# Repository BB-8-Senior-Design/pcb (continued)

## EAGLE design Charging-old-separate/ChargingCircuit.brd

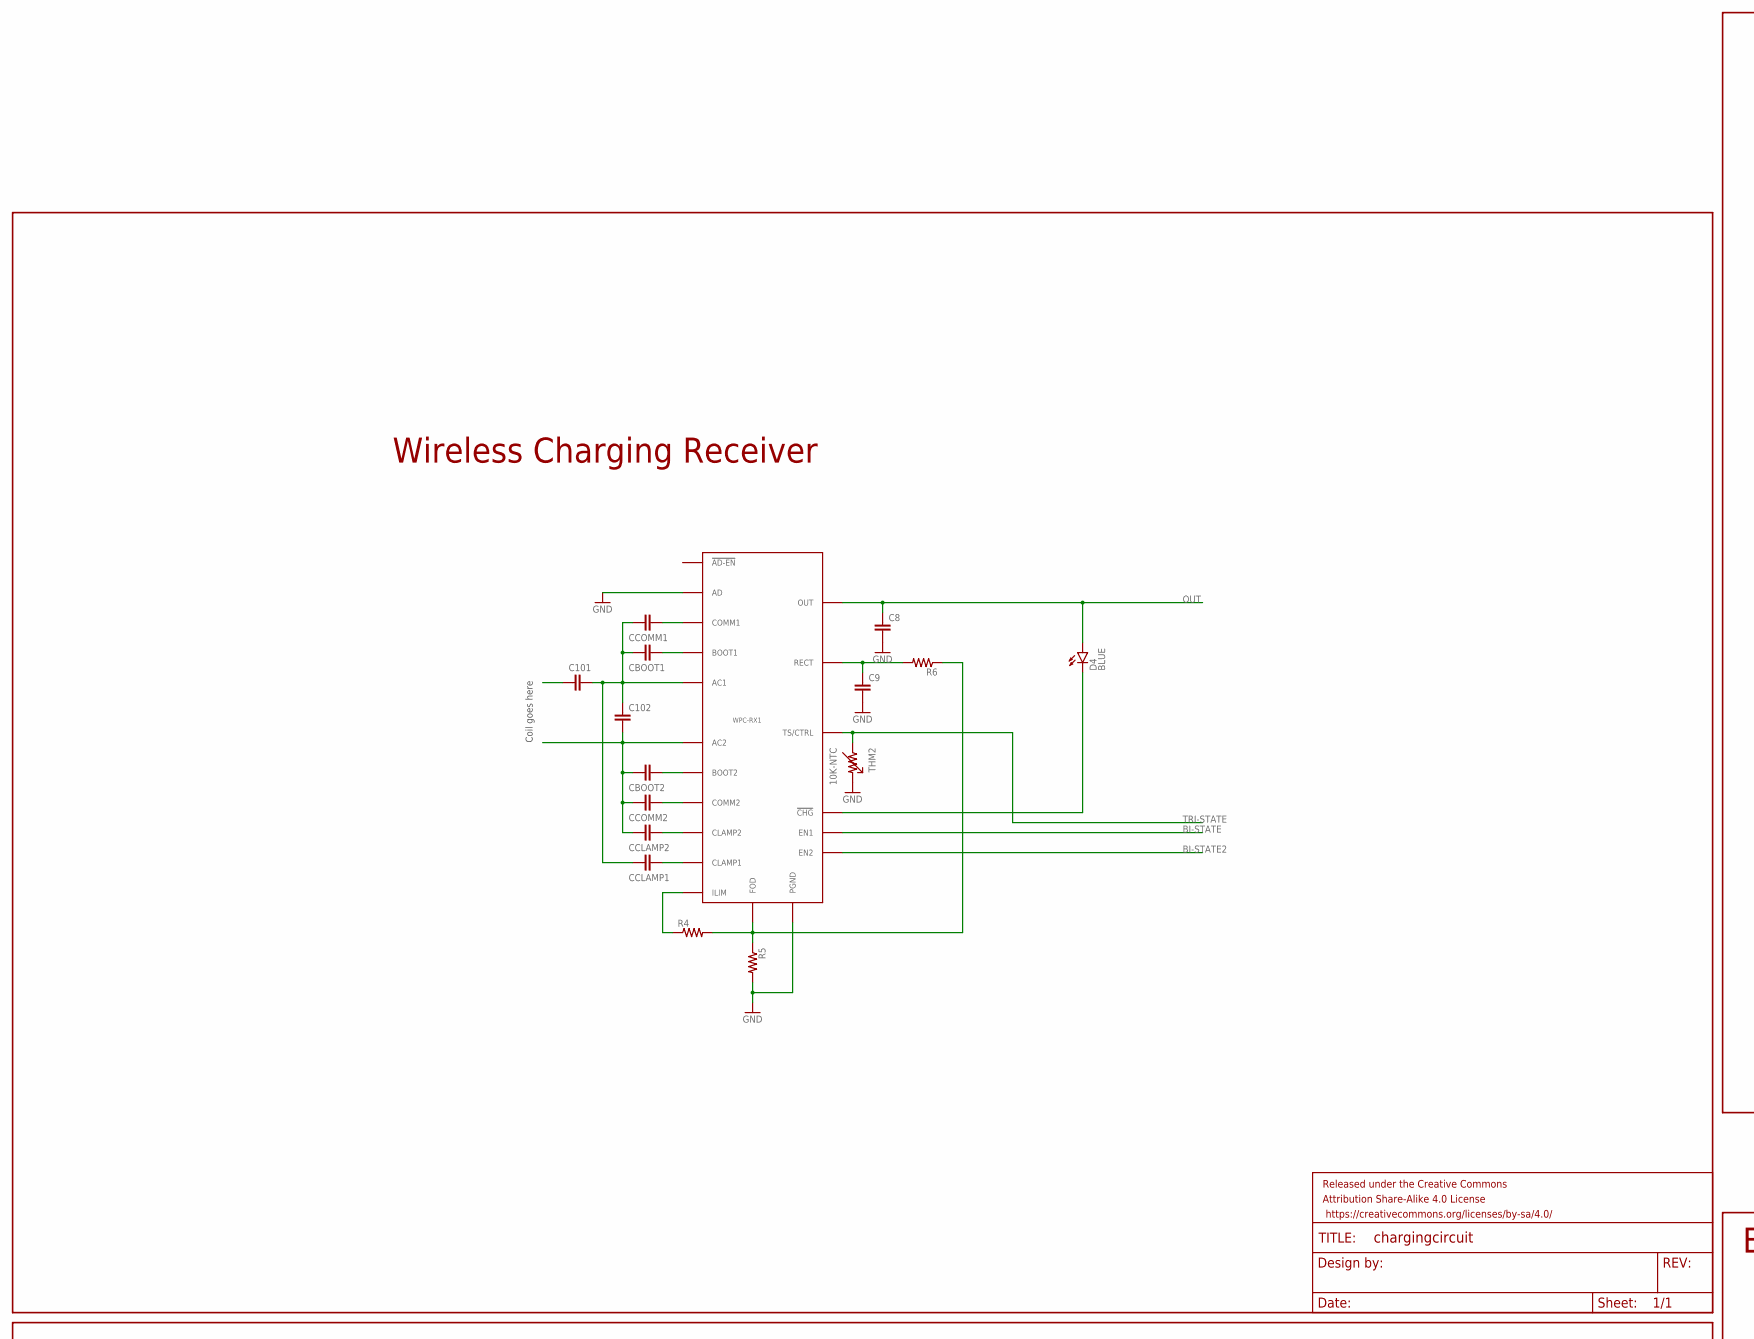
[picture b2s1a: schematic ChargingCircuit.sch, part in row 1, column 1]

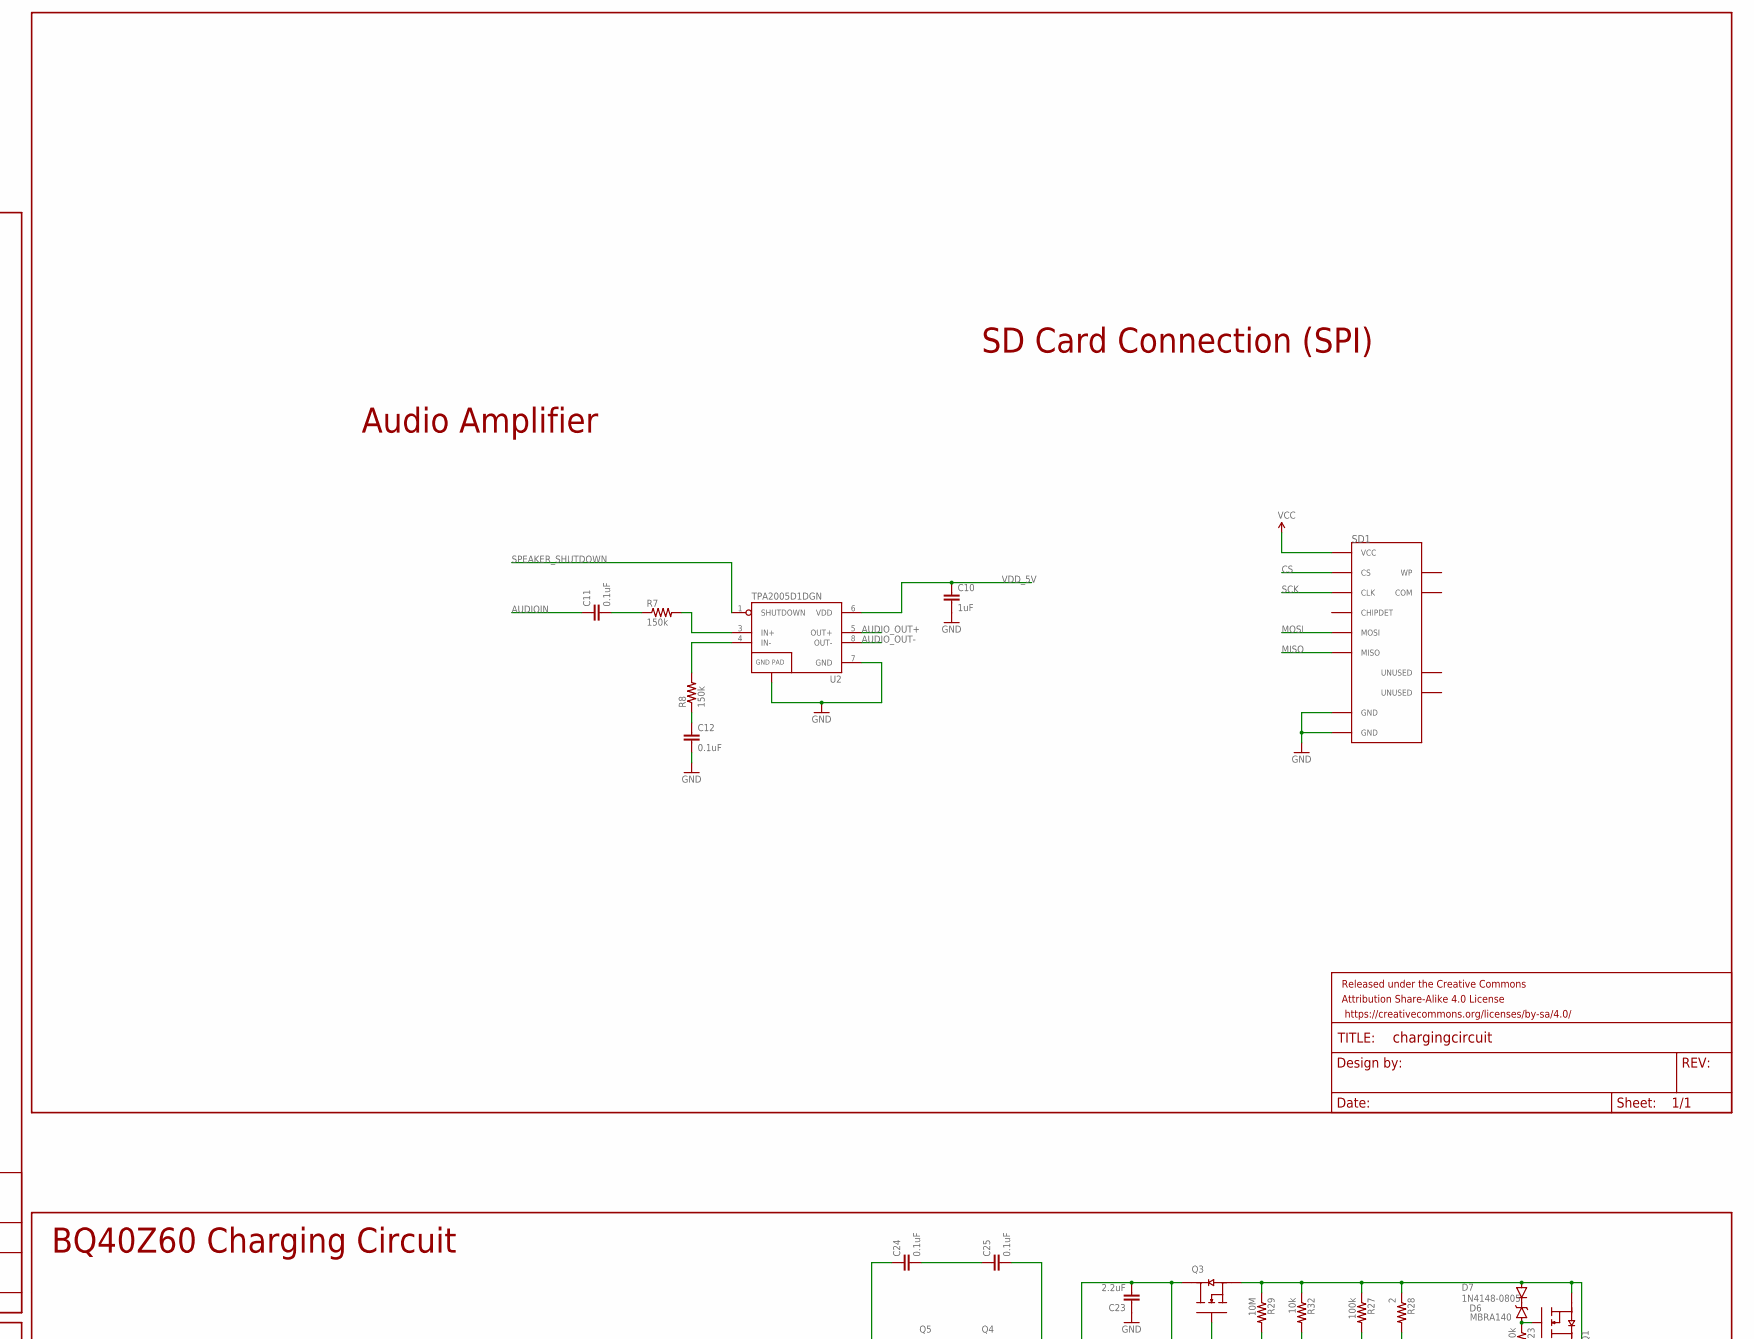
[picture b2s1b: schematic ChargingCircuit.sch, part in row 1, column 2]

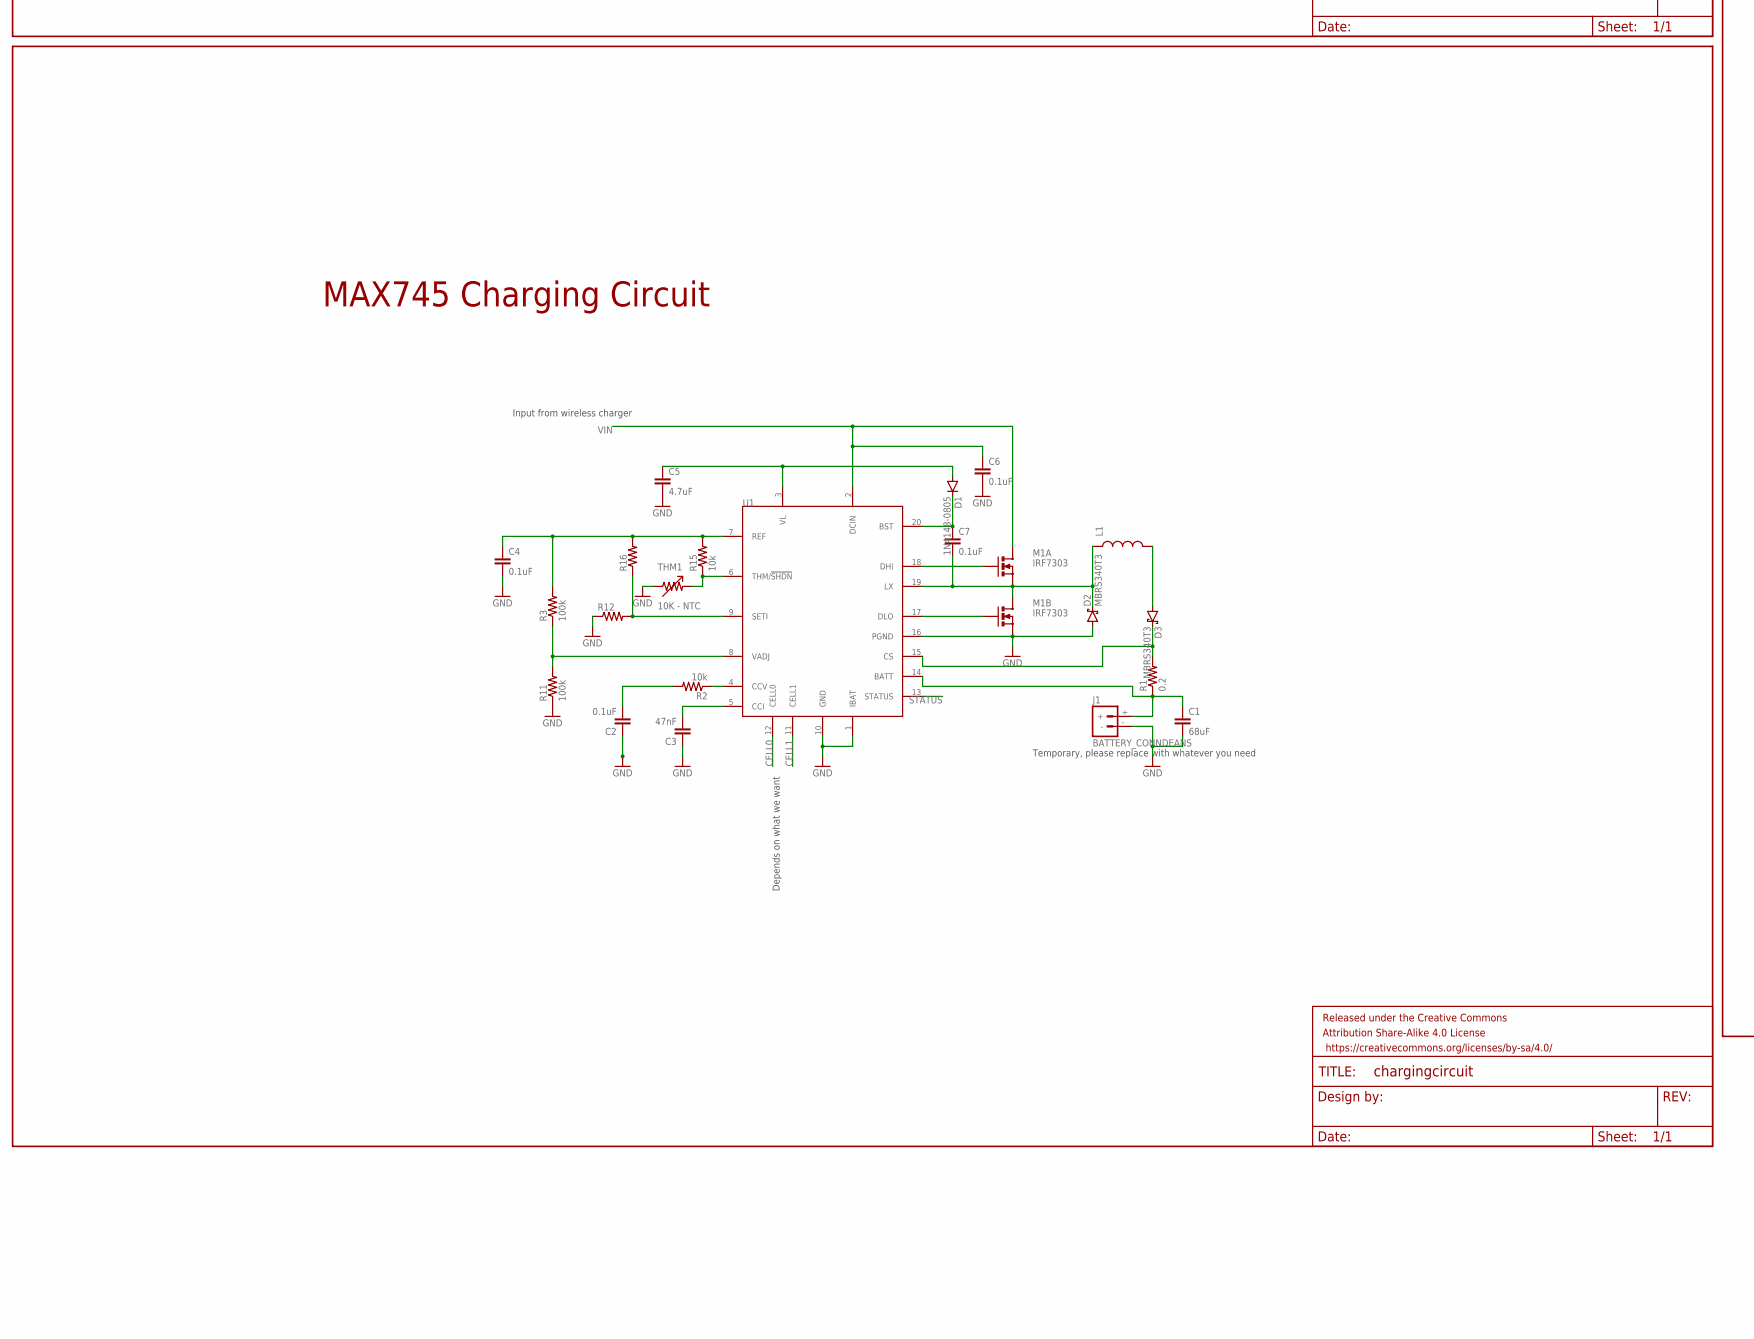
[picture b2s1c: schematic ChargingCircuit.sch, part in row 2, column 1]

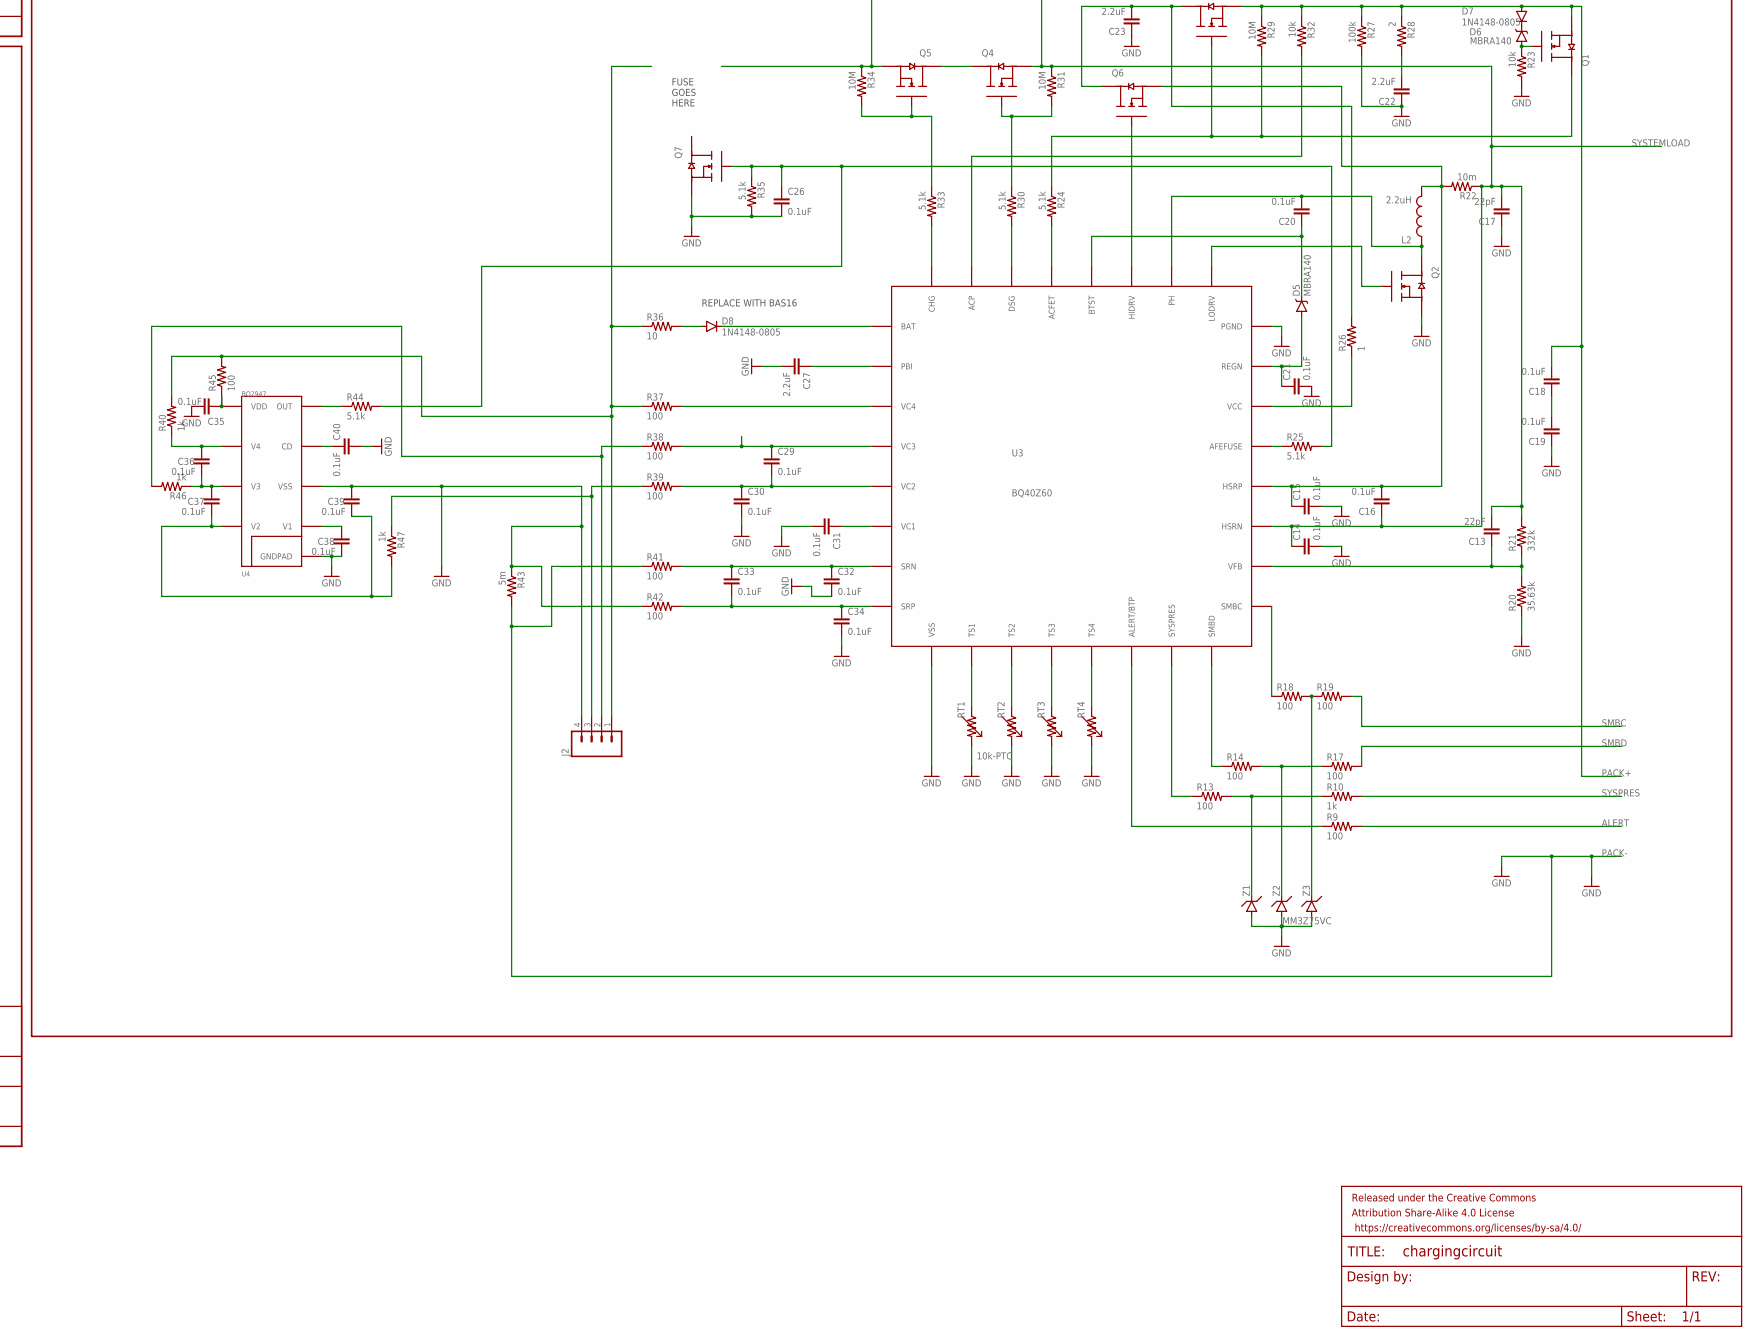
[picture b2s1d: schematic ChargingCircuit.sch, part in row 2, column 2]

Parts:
C1: 68uF; 0805
C2, C4, C6, C7, C11, C12, C14, C15, C16, C18, C19, C20, C21, C24, C25, C26, C29, C30, C31, C32, C33, C34, C35, C36, C37, C38, C39, C40: 0.1uF; 0805
C3: 47nF; 0805
C5: 4.7uF; 0805
C8, C9, C101, C102: CAP0805; 0805
C10: 1uF; 0805
C13, C17: 22pF; 0805
C22, C23, C27: 2.2uF; 0805
CBOOT1, CBOOT2: CAP0805; 0805
CCLAMP1, CCLAMP2: CAP0805; 0805
CCOMM1, CCOMM2: CAP0805; 0805
D1, D7, D8: 1N4148-0805; 0805-DIODE
D2, D3: MBRS340T3; DO-214AB
D4: BLUE; LED-0603
D5, D6: MBRA140; SMA-DIODE
FRAME6, FRAME7, FRAME8, FRAME9: FRAME-LEDGER; CREATIVE_COMMONS
J1: BATTERY_CONNDEANS; DEANS
J2: M04JST; 1X04-1.5MM_JST
L1: INDUCTOR0805; 0805
L2: 2.2uH; 0805
M1: IRF7303; SO08
Q1, Q2, Q3, Q4, Q5, Q6, Q7: CSD17308Q3; SON-8
R1: 0.2; 0805
R2, R15, R23, R32: 10k; 0805
R3, R11, R27: 100k; 0805
R4, R5, R6, R12, R16: RESISTOR0805-RES; 0805
R7, R8: 150k; 0805
R9, R13, R14, R17, R18, R19, R37, R38, R39, R41, R42, R45: 100; 0805
R10, R40, R46, R47: 1k; 0805
R20: 35.63k; 0805
R21: 332k; 0805
R22: 10m; 0805
R24, R25, R30, R33, R35, R44: 5.1k; 0805
R26: 1; 0805
R28: 2; 0805
R29, R31, R34: 10M; 0805
R36: 10; 0805
R43: 5m; 0805
RT1: 10k-PTC; 0805
RT2, RT3, RT4: THM; 0805
SD1: 5738-SDCARD; SD-5738
THM1: 10K - NTC; 0805
THM2: 10K-NTC; 0805
U1: MAX745EACSSOP; SSOP20
U2: TPA2005D1DGN; POWER-SOP8
U3: BQ40Z60; S-PVQFN-N32
U4: BQ2947; WSON-8
WPC-RX1: BQ51013B-20VQFN; 20-VQFN
Z1, Z2, Z3: MM3Z75VC; SOD-323F

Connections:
AC1: C101.2, C102.1, CBOOT1.1, CCLAMP1.1, CCOMM1.1, WPC-RX1.P$2 (AC1)
AC2: C102.2, CBOOT2.1, CCLAMP2.1, CCOMM2.1, WPC-RX1.P$19 (AC2)
ALERT: R9.2
AUDIOIN: C11.1
AUDIO_OUT+: U2.5 (OUT+)
AUDIO_OUT-: U2.8 (OUT-)
BI-STATE: WPC-RX1.P$10 (EN1)
BI-STATE2: WPC-RX1.P$11 (EN2)
BOOT2: CBOOT2.2, WPC-RX1.P$17 (BOOT2)
CELL0: U1.12 (CELL0)
CELL1: U1.11 (CELL1)
CS: SD1.P$1 (CS)
GND: C1.2, C2.1, C3.1, C4.2, C5.2, C6.2, C8.2, C9.2, C10.2, C12.2, C14.2, C15.2, C17.1, C19.1, C21.2, C22.1, C23.1, C26.2, C27.2, C30.2, C31.2, C32.2, C34.2, C35.2, C38.2, C39.1, C40.2, D2.POS (A), J1.-, J2.4, M1.3 (S), Q2.P$1 (S1), Q2.P$2 (S1), Q2.P$3 (S1), Q7.P$1 (S1), Q7.P$2 (S1), Q7.P$3 (S1), R5.2, R11.1, R12.1, R20.1, R23.2, R27.2, R35.2, R42.1, R43.1, RT1.2, RT2.2, RT3.2, RT4.2, SD1.P$3 (GND), SD1.P$6 (GND), THM1.1, THM2.2, U1.1 (IBAT), U1.10 (GND), U1.16 (PGND), U2.7 (GND), U2.9 (GND), U3.P$9 (VSS), U3.P$24 (PGND), U3.P$GND (VSS), U4.P$6 (VSS), U4.P$GND (GNDPAD), WPC-RX1.P$1 (PGND), WPC-RX1.P$9 (AD), WPC-RX1.P$20 (PGND), Z1.1 (A), Z2.1 (A), Z3.1 (A)
MISO: SD1.P$7 (MISO)
MOSI: SD1.P$2 (MOSI)
unnamed: C5.1, D1.1 (A), U1.3 (VL)
unnamed: C7.1, D1.2 (C), U1.20 (BST)
unnamed: M1.2 (G), U1.18 (DHI)
unnamed: M1.4 (G), U1.17 (DLO)
unnamed: D3.NEG (C), R1.2, U1.15 (CS)
unnamed: D3.POS (A), L1.2
unnamed: C1.1, J1.+, R1.1, U1.14 (BATT)
unnamed: C7.2, D2.NEG (C), L1.1, M1.1 (S), M1.5 (D), M1.6 (D), U1.19 (LX)
unnamed: C3.2, U1.5 (CCI)
unnamed: R2.1, U1.4 (CCV)
unnamed: C2.2, R2.2
unnamed: C4.1, R3.2, R15.2, R16.2, U1.7 (REF)
unnamed: R12.2, R16.1, U1.9 (SETI)
unnamed: R15.1, THM1.2, U1.6 (THM/!SHDN)
unnamed: R3.1, R11.2, U1.8 (VADJ)
unnamed: CCOMM2.2, WPC-RX1.P$15 (COMM2)
unnamed: CCLAMP2.2, WPC-RX1.P$16 (CLAMP2)
unnamed: CCLAMP1.2, WPC-RX1.P$5 (CLAMP1)
unnamed: CBOOT1.2, WPC-RX1.P$3 (BOOT1)
unnamed: CCOMM1.2, WPC-RX1.P$6 (COMM1)
unnamed: R4.1, WPC-RX1.P$12 (ILIM)
unnamed: R4.2, R5.1, R6.1, WPC-RX1.P$14 (FOD)
unnamed: D4.C, WPC-RX1.P$7 (!CHG)
unnamed: C9.1, R6.2, WPC-RX1.P$18 (RECT)
unnamed: R7.2, U2.3 (IN+)
unnamed: C11.2, R7.1
unnamed: R10.1, R13.2, Z1.2 (C)
unnamed: R8.2, U2.4 (IN-)
unnamed: RT1.1, U3.P$10 (TS1)
unnamed: C12.1, R8.1
unnamed: RT2.1, U3.P$11 (TS2)
unnamed: RT3.1, U3.P$12 (TS3)
unnamed: RT4.1, U3.P$13 (TS4)
unnamed: R9.1, U3.P$14 (ALERT/BTP)
unnamed: Q1.P$5 (D1), Q1.P$6 (D1), Q1.P$7 (D1), Q1.P$8 (D1), Q3.P$4 (G1), R24.1, R29.2
unnamed: R13.1, U3.P$15 (SYSPRES)
unnamed: R14.1, U3.P$16 (SMBD)
unnamed: R14.2, R17.1, Z2.2 (C)
unnamed: C13.1, R20.2, R21.1, U3.P$18 (VFB)
unnamed: R24.2, U3.P$29 (ACFET)
unnamed: C18.1, C19.2
unnamed: R18.1, U3.P$17 (SMBC)
unnamed: R18.2, R19.1, Z3.2 (C)
unnamed: C15.1, C16.2, L2.2, Q6.P$1 (S1), Q6.P$2 (S1), Q6.P$3 (S1), R22.2, U3.P$20 (HSRP)
unnamed: R26.1, U3.P$22 (VCC)
unnamed: D6.A, Q1.P$4 (G1), R23.1
unnamed: C20.2, L2.1, Q2.P$5 (D1), Q2.P$6 (D1), Q2.P$7 (D1), Q2.P$8 (D1), U3.P$26 (PH)
unnamed: C20.1, D5.C, U3.P$28 (BTST)
unnamed: C21.1, D5.A, U3.P$23 (REGN)
unnamed: C23.2, Q3.P$5 (D1), Q3.P$6 (D1), Q3.P$7 (D1), Q3.P$8 (D1), Q6.P$5 (D1), Q6.P$6 (D1), Q6.P$7 (D1), Q6.P$8 (D1), R26.2
unnamed: R25.1, U3.P$21 (AFEFUSE)
unnamed: C26.1, Q7.P$4 (G1), R25.2, R35.1, R44.2
unnamed: Q6.P$4 (G1), U3.P$27 (HIDRV)
unnamed: D6.C, D7.2 (C)
unnamed: C22.2, R28.2
unnamed: Q2.P$4 (G1), U3.P$25 (LODRV)
unnamed: R30.2, U3.P$31 (DSG)
unnamed: Q4.P$4 (G1), R30.1, R31.2
unnamed: R32.2, U3.P$30 (ACP)
unnamed: Q4.P$5 (D1), Q4.P$6 (D1), Q4.P$7 (D1), Q4.P$8 (D1), Q5.P$5 (D1), Q5.P$6 (D1), Q5.P$7 (D1), Q5.P$8 (D1)
unnamed: C24.2, C25.1
unnamed: C24.1, Q5.P$1 (S1), Q5.P$2 (S1), Q5.P$3 (S1), R34.1
unnamed: Q5.P$4 (G1), R33.1, R34.2
unnamed: R33.2, U3.P$32 (CHG)
unnamed: C40.1, U4.P$7 (CD)
unnamed: J2.1, R36.1, R37.1, R40.2, R45.2
unnamed: D8.2 (C), U3.P$1 (BAT)
unnamed: D8.1 (A), R36.2
unnamed: C27.1, U3.P$2 (PBI)
unnamed: R37.2, U3.P$3 (VC4)
unnamed: C29.1, R38.2, U3.P$4 (VC3)
unnamed: C29.2, C30.1, R39.2, U3.P$5 (VC2)
unnamed: C31.1, U3.P$6 (VC1)
unnamed: C32.1, C33.1, R41.2, U3.P$7 (SRN)
unnamed: C33.2, C34.1, R42.2, U3.P$8 (SRP)
unnamed: R44.1, U4.P$8 (OUT)
unnamed: C36.1, R40.1, U4.P$2 (V4)
unnamed: J2.2, R38.1, R46.2
unnamed: J2.3, R39.1, R47.1
unnamed: C35.1, R45.1, U4.P$1 (VDD)
unnamed: C36.2, C37.1, R46.1, U4.P$3 (V3)
unnamed: C37.2, C39.2, R47.2, U4.P$4 (V2)
unnamed: C38.1, U4.P$5 (V1)
OUT: C8.1, D4.A, WPC-RX1.P$4 (OUT)
PACK+: C18.2, D7.1 (A), Q1.P$1 (S1), Q1.P$2 (S1), Q1.P$3 (S1), Q3.P$1 (S1), Q3.P$2 (S1), Q3.P$3 (S1), R27.1, R28.1, R29.1, R32.1
PACK-: R41.1, R43.2
SCK: SD1.P$5 (CLK)
SMBC: R19.2
SMBD: R17.2
SPEAKER_SHUTDOWN: U2.1 (SHUTDOWN)
STATUS: U1.13 (STATUS)
SYSPRES: R10.2
SYSTEMLOAD: C13.2, C14.1, C16.1, C17.2, C25.2, Q4.P$1 (S1), Q4.P$2 (S1), Q4.P$3 (S1), R21.2, R22.1, R31.1, U3.P$19 (HSRN)
TRI-STATE: THM2.1, WPC-RX1.P$13 (TS/CTRL)
VDD_5V: C10.1, U2.6 (VDD)
VIN: C6.1, M1.7 (D), M1.8 (D), U1.2 (DCIN)

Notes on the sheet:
MAX745 Charging Circuit
Wireless Charging Receiver
Audio Amplifier
Temporary, please replace with whatever you need
Coil goes here
Input from wireless charger
Depends on what we want
SD Card Connection (SPI)
BQ40Z60 Charging Circuit
REPLACE WITH BAS16
FUSE GOES HERE

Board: 2 copper layers, 133 parts (0 on the bottom side), 94 nets, no tracks yet.

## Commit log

2016-09-17 Initial board
2016-09-18 stuff
2016-09-18 Added more parts
2016-09-18 Added MAX745 circuit to pcb project
2016-09-18 Updated board
2016-09-18 minor changes to charging board
2016-09-19 Started powering micro
2016-09-19 Labeling MCs
2016-09-19 Added leve; translation for motor stuff
2016-09-21 Added oscilator to schematic
2016-09-21 Added wireless charging board, speaker circuit
2016-09-22 Added most remaining STM requirements
2016-09-22 added more info for boards
2016-09-22 added extra oscillator resistor
2016-09-23 More work on SD card stuff; TODO: finish up calculations for charging circuit values
2016-09-23 updated crystals
2016-09-23 added buck regulator
2016-09-23 added jtag
2016-09-23 started adding motors
2016-09-23 finished adding motors
2016-09-23 Added cap values
2016-09-23 Moved parts onto board
2016-09-23 Added BQ40Z60 Charging Circuit
2016-09-23 added IMU
2016-09-23 Preliminary work on BQ40Z60, need to short VC3 and VC4, fix VC1
2016-09-23 Combined boards -- death
2016-09-23 Fixed BQ40Z60 for 3S configuration
2016-09-23 Updated symbols for some parts to show value too
2016-09-23 Moved old charging circuit to directory
2016-09-28 Fixed Charging board 3S connections, connected EVERYTHING to the micro
2016-09-28 Various updates to the board
2016-09-30 Updated some values
2016-10-01 Addded fuses to charger, need to finish
2016-10-03 Finalized parts
2016-10-03 added heartbeat LED to PC13
2016-10-03 Replaced inductor in buck regulator
2016-10-03 Renumbered ALL elements
2016-10-03 Minor moving around
2016-10-03 Preliminary layout for wireless receiver done
2016-10-03 More board movement, things are now more or less clustered now
2016-10-03 More moving things around
2016-10-05 replaced SPI sd to SDIO
2016-10-05 fixed board size
2016-10-05 added switch
2016-10-05 started traces
2016-10-05 initial layout of charging circuit
2016-10-05 added XT60
2016-10-05 Moved the schematic
2016-10-05 LAYOUT AAAAAAAAAAAAAAAAAAAAAAAAAAAAAAAAAAAAAAAAAAAAAAAAAAAAAAAAAAAAAAAAAAAAAAAAAAAAAAAAAAAAAAAAAAAAAAAAAAAAAAAAAAAAAAAAAAAAAAAAAAAAAAAAAAAAAAAAAAAAAAARRRRRRRRRRRRRRRRRRRRRRRRRRRRRRRRRRRRRRRRRGGGGGGGG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
2016-10-06 MORE LAYOUT OH GOD EVERYTHING IS GOING TO FAIL
2016-10-06 removed CC-by-SA text from board
2016-10-06 Smaller vias make me happy
2016-10-06 Minor routing progress. TODO: layout for micro parts
2016-10-06 I... I think I finished routing the charging circuit...
2016-10-06 Added Advanced Circuits design rules
2016-10-06 Changed some rects to pads
2016-10-11 routed and placed decoupling capacitors for micro
2016-10-12 continued power routing and more
2016-10-12 rearranged some stuff
2016-10-12 so much routing
2016-10-12 routed mostly everything
2016-10-12 stuff\
2016-10-13 Fixed via sizes, made routes slightly better angles (thanks, kyle)
2016-10-13 more routing fixes
2016-10-13 Added design rule checker, moved some stuff for clearance
2016-10-13 More minor fixes for the DRC, rerouting things so it doesn't yell at me (as much)
2016-10-13 Fixed 3 drill sizes
2016-10-13 AdRedid gnd to pgnd for wireless charging circuit
2016-10-14 Changed DRC to be 5mil
2016-10-14 Down to 33 clearance errors
2016-10-14 Removed ALL violations
2016-10-14 Fixed overlap issue caused by resizing
2016-10-14 Modified capacitor sizes
2016-10-15 routed LED, added standoffs, and refined routes
2016-10-15 Updated cap pads to be slightly larager for easy soldering
2016-10-15 Removed LEDs and 3 pin header since it wasn't worth trying to route
2016-10-15 added vias connecting top and bottom planes (also CAM output)
2016-10-15 manually added new keepout layers and tstop (Chris check)
2016-10-16 Added thermal vias and rerouted some stuff
2016-10-16 moved passives on speaker IC closer
2016-10-16 fixed clearance errors due to ground planes
2016-10-16 Removed vias from power mosfet
2016-10-16 Final part and layout updates (hopefully)
2016-10-16 added trestrict
2016-10-17 Fixed clearance issues and uploaded new Gerbers
2016-10-17 added another main fuse
2016-10-17 added 3-pole LPF w/cutoff ~16kHz
2016-10-17 slightly larger cap size
2016-10-17 added soldermask to SD pad
2016-10-17 Fixed hole sizes
2016-10-17 made SMB clock longer
2016-10-18 added current limiting resistor
2016-10-18 added cap between V1 and V2 of charging circuit
2016-10-18 final final actually final iteration pls god
2016-11-06 new branch
2016-11-06 removed lots of components
2016-11-06 Added pullup resistors to SD card holder lol
2016-11-06 Added pullup resistor to audio amp circuit and adjusted capacitor values
2016-11-06 Kyle spelled my name wrong
2016-11-06 Made board straight and minor routing
2016-11-06 Changed some weird routes to ground
2016-11-07 Added test points to speaker system
2016-11-07 Added BB-8, made holes in JST-XH connector larger
2016-11-07 Finished board v2???
2016-11-07 Made board straight because kyle why
2016-11-08 added connections to future battery board
2016-11-08 minor angle fixes
2016-11-08 Finished up text for our names
2016-11-08 update from sd-card holes
2016-11-08 moved some tValues and tPlace things around
2016-11-09 Minor adjustments to spacing
2016-11-10 moved some stuff around, kyle please check the board for any final adjustments
2016-11-10 Made board smaller, finished routing, added new test via, ect.
2016-11-10 made SD card traces closer in length
2016-11-10 Gerbers, new DRU, and finished board (hopefully)
2016-11-10 Added decoupling caps near level translators
2016-11-11 updated the library
2016-11-14 Final gerbers
